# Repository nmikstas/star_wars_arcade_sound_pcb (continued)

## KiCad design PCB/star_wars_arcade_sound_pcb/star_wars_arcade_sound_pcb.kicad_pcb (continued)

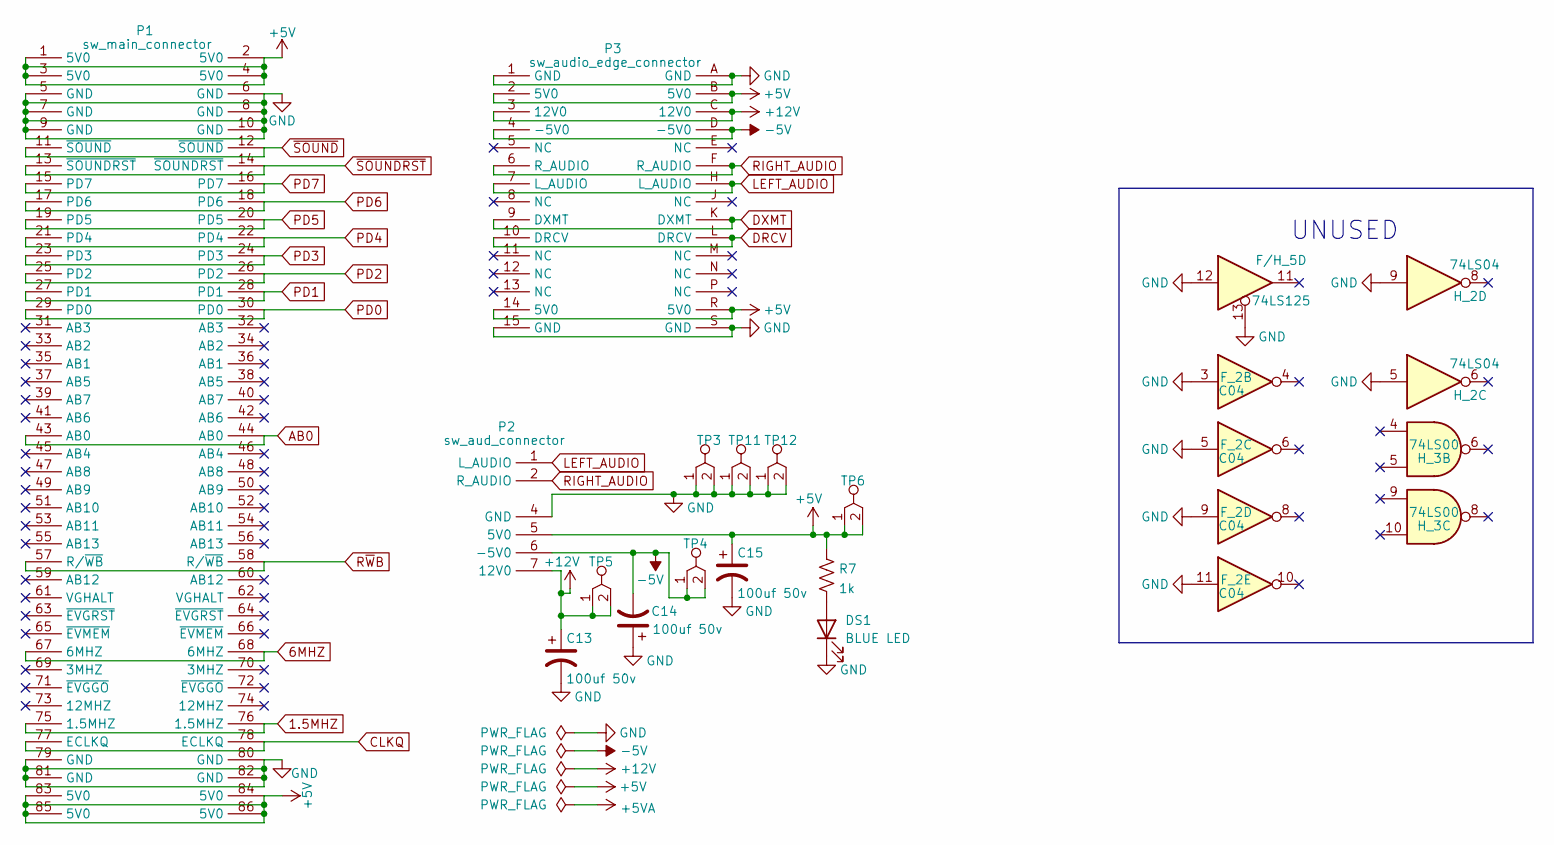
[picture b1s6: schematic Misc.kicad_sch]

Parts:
C13, C15: 100uf 50v; LargeCap1
C14: 100uf 50v; LargeCap2
DS1: BLUE LED; LED
F/H_5: 74LS125; DIP14
F_2: C04; DIP14
H_2: 74LS04; DIP14
H_3: 74LS00; DIP14
P1: sw_main_connector; P1
P2: sw_aud_connector; Aud_Con
P3: sw_audio_edge_connector; P3
R7: 1k; GenericComp
TP3, TP4, TP5, TP6, TP11, TP12: tp_2_pin; TEST_POINT

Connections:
1.5MHZ: P1.75 (1.5MHZ), P1.76 (1.5MHZ); also elsewhere on the board
6MHZ: P1.67 (6MHZ), P1.68 (6MHZ); also elsewhere on the board
+5V: C15.1, P1.1 (5V0), P1.2 (5V0), P1.3 (5V0), P1.4 (5V0), P1.83 (5V0), P1.84 (5V0), P1.85 (5V0), P1.86 (5V0), P2.5 (5V0), P3.2 (5V0), P3.14 (5V0), P3.B (5V0), P3.R (5V0), R7.1, TP6.1, TP6.2; also elsewhere on the board
+12V: C13.1, P2.7 (12V0), P3.3 (12V0), P3.C (12V0), TP5.1, TP5.2; also elsewhere on the board
-5V: C14.2, P2.6 (-5V0), P3.4 (-5V0), P3.D (-5V0), TP4.1, TP4.2; also elsewhere on the board
AB0: P1.43 (AB0), P1.44 (AB0); also elsewhere on the board
CLKQ: P1.77 (ECLKQ), P1.78 (ECLKQ); also elsewhere on the board
DRCV: P3.10 (DRCV), P3.L (DRCV); also elsewhere on the board
DXMT: P3.9 (DXMT), P3.K (DXMT); also elsewhere on the board
GND: C13.2, C14.1, C15.2, DS1.1 (K), F/H_5.12, F/H_5.13, F_2.3, F_2.5, F_2.9, F_2.11, H_2.5, H_2.9, P1.5 (GND), P1.6 (GND), P1.7 (GND), P1.8 (GND), P1.9 (GND), P1.10 (GND), P1.79 (GND), P1.80 (GND), P1.81 (GND), P1.82 (GND), P2.4 (GND), P3.1 (GND), P3.15 (GND), P3.A (GND), P3.S (GND), TP3.1, TP3.2, TP11.1, TP11.2, TP12.1, TP12.2; also elsewhere on the board
LEFT_AUDIO: P2.1 (L_AUDIO), P3.7 (L_AUDIO), P3.H (L_AUDIO); also elsewhere on the board
unnamed: DS1.2 (A), R7.2
PD0: P1.29 (PD0), P1.30 (PD0); also elsewhere on the board
PD1: P1.27 (PD1), P1.28 (PD1); also elsewhere on the board
PD2: P1.25 (PD2), P1.26 (PD2); also elsewhere on the board
PD3: P1.23 (PD3), P1.24 (PD3); also elsewhere on the board
PD4: P1.21 (PD4), P1.22 (PD4); also elsewhere on the board
PD5: P1.19 (PD5), P1.20 (PD5); also elsewhere on the board
PD6: P1.17 (PD6), P1.18 (PD6); also elsewhere on the board
PD7: P1.15 (PD7), P1.16 (PD7); also elsewhere on the board
RIGHT_AUDIO: P2.2 (R_AUDIO), P3.6 (R_AUDIO), P3.F (R_AUDIO); also elsewhere on the board
R~WB: P1.57 (R/~WB), P1.58 (R/~WB); also elsewhere on the board
~SOUNDRST: P1.13 (~SOUNDRST), P1.14 (~SOUNDRST); also elsewhere on the board
~SOUND: P1.11 (~SOUND), P1.12 (~SOUND); also elsewhere on the board

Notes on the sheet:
UNUSED

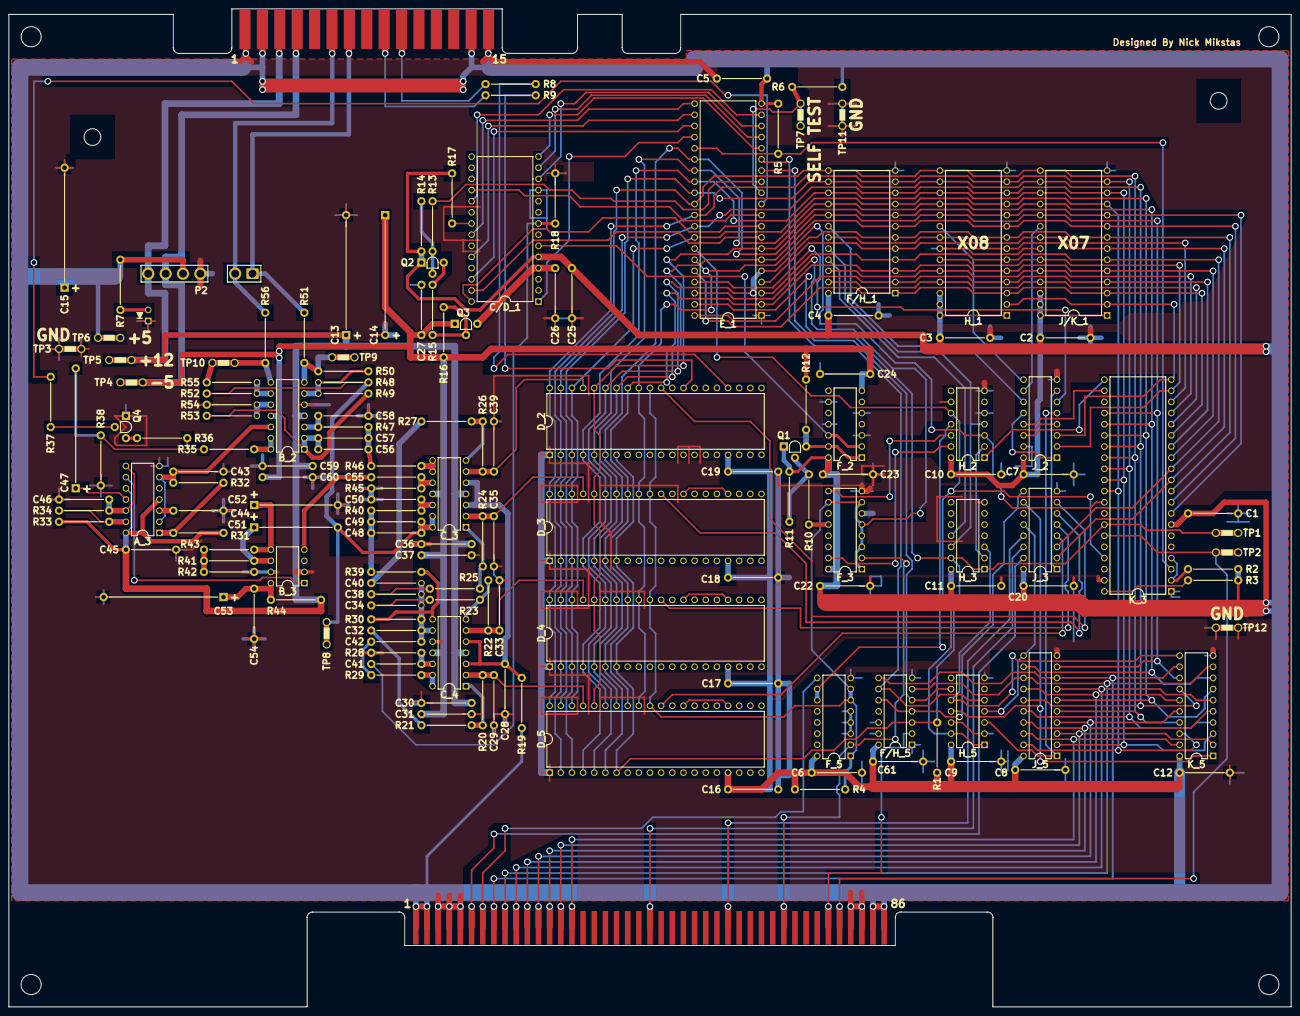
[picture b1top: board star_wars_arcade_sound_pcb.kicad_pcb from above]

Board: 2 copper layers, 292.1 x 227.3 mm, 162 parts (0 on the bottom side), 154 nets.

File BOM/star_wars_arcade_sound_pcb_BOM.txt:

Part_ID                                                 QTY     DESC            Part_Num

C1,  C2,  C3,  C4,  C5,  C6,  C7,  C8,  C9,  C10,       41      0.1uf           Digikey 399-4454-1-ND
C11, C12, C16, C17, C18, C19, C20, C22, C23, C24,
C25, C26, C27, C28, C30, C37, C38, C40, C41, C42,
C43, C45, C54, C55, C59, C60, C61, C31, C32, C34,
C36
C46, C48, C49, C50, C56, C57, C58                       7       0.0027uf        Digikey 478-11573-1-ND
C13, C14, C15, C47, C53		                            5       100uf 50V       Digikey 1572-1309-ND
C29, C33, C35, C39                                      4       1000pf          Digikey 1216PHCT-ND
C44                                                     1       0.01uf          Digikey 399-4452-1-ND
C51                                                     1       0.47uf          Digikey 1572-1461-ND‎
C52                                                     1       10uf            Digikey 1572-1294-ND

DS1                                                     1       BLUE LED        Digikey VAOL-5701SBY4-ND

P2                                                      1       7 pin con       Digikey A19878-ND‎

Q1, Q2                                                  2       2N3906          Digikey 2N3906TAFSCT-ND
Q3, Q4                                                  2       2N3904          Digikey 2N3904TAFSCT-ND

R1,  R4,  R7,  R12, R15, R20, R22, R24, R26             9       1K              Digikey 1.0KQBK-ND
R2,  R3,  R5,  R6,  R10, R13, R17, R37                  8       10K             Digikey 10KQBK-ND
R30, R39, R40, R42, R46, R47                            6       12K             Digikey 12KQBK-ND
R21, R23, R50, R54, R55                                 5       47K             Digikey 47KQBK-ND
R48, R49, R52, R53                                      4       22K             Digikey 22KQBK-ND
R35, R51, R56                                           3       2.2K            Digikey 2.2KQBK-ND
R8,  R9,  R44                                           3       100             Digikey 100QBK-ND
R11, R14, R16                                           3       3.3K            Digikey 3.3KQBK-ND
R25, R27                                                2       82K             Digikey 82KQBK-ND
R33, R34                                                2       4.7K            Digikey 4.7KQBK-ND
R31, R32                                                2       560K            Digikey 560KQBK-ND
R19, R28                                                2       100K            Digikey 100KQBK-ND
R18                                                     1       1.8K            Digikey 1.8KQBK-ND
R29                                                     1       15K             Digikey 15KQBK-ND
R36                                                     1       15              Digikey 15QBK-ND
R38                                                     1       470             Digikey 470QBK-ND
R41                                                     1       68K             Digikey 68KQBK-ND
R43                                                     1       1.5K            Digikey 1.5KQBK-ND
R45                                                     1       470K            Digikey 470KQBK-ND

TP1,  TP2, TP3, TP4, TP5, TP6, TP7, TP8, TP9, TP10      12      Test Point      Digikey WM6456-ND
TP11, TP12

D-2, D-3, D-4, D-5                                      4       POKEY           Ebay
B-2, C-3, C-4                                           3       TL084           Digikey 296-1782-5-ND‎
H-1, J/K-1                                              2       2764            Jameco 2303119
F-3, F-5                                                2       LS161           Digikey 296-1646-5-ND
J-2, J-3                                                2       LS139           Digikey 296-1640-5-ND
J-5, K-5                                                2       LS374           Jameco 47634
C/D-1                                                   1       TMS-5220        Ebay
F/H-1                                                   1       6116-2K-RAM     Jameco 242675
F/H-5                                                   1       LS125           Jameco 46501
E-1                                                     1       PIA             Ebay
F-2                                                     1       CD4069/74C04    Jameco 13231
A-3                                                     1       NE556           Jameco 904114
B-3                                                     1       R5106           Ebay
H-2                                                     1       LS04            Jameco 46316
H-3                                                     1       LS00            Jameco 46252
H-5                                                     1       LS74            Jameco 48004
K-3                                                     1       6809E           Ebay

IC Sockets
-------------------
8  pin     1
14 pin     9
16-pin     4
20-pin     2
24-pin     1
28-pin     3
40-pin     6

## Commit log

2022-04-12 Worked on schematics
2022-04-12 Finished schematic
2022-04-12 Began PCB layout
2022-04-12 ICs placed
2022-04-13 Placed all components
2022-04-13 Silkscreen work
2022-04-13 Trace work
2022-04-14 374 connections remain
2022-04-15 331 connections remain
2022-04-15 285 connections remain
2022-04-16 189 connections remain
2022-04-16 Ground plane and mounting holes remain
2022-04-17 Bottom ground plane and mounting holes remain
2022-04-18 Bottom keep out areas remain
2022-04-20 Consolidated keep out areas
2022-04-21 Completed PCB
2022-04-21 Added gerbers
2022-04-21 Updated readme file
2022-05-02 Updated schematic
